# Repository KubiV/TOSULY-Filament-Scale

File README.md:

# TOSULY ALFA (V0.1)
## _DIY Filament scale integrated into filament holder_

Do It Yourself Filament Spool Scale which is integrated into the filament holder so you can easily monitor your remaining filament. By default it is not using batteries so you can hook it up straight to the printer/power suply. Optionaly you can add battery by soldering extension wires to prepared pads and than attach battery. 

## Features

- Open-source
- Custom PCB
- OLED 0.96 inch display
- Buttons (one under the display so it clicks when you push the display)
- By double-clicking button subtract spool dry mass
- Powered by Arduino Nano
- Compatible with stock Ender 3 spool holder, Prusa Original frame

## Needed

- 4x M3 screws (15mm for mounting PCBs)
- 2x M3 nuts (rectangle PCB mounting)
- 4x M4 screws (approx. 10 mm, and 2 with flat head)
- Custom PCB
- 7x1 horizontal pin header 2.54 mm pitch
- Arduino Nano
- USB cable (according on Arduino Nano variant)
- A DC-DC step-down converter and USB port for connecting the USB cable
- Load Cell 5 kg
- HX711 AD Module Weight Sensor
- 0.96 Inch OLED Module I2C
- 3x buttons 6 mm
- 3 resistor axial
- 3D printed parts (Upper, Body, Nut, Cover)

## Load cell

Compatible with both load cell designs - 12.7 x 12.7 x 75mm (type 1) or 12.7 x 12.7 x 80mm (type 2), holes for M4 bolts and two holes for M5 holes (type 2).

## 3D Printable parts

Mounting screw has 24 mm i diameter with according thread.

V02 design inspired by https://youtu.be/WO-hR7okl3k

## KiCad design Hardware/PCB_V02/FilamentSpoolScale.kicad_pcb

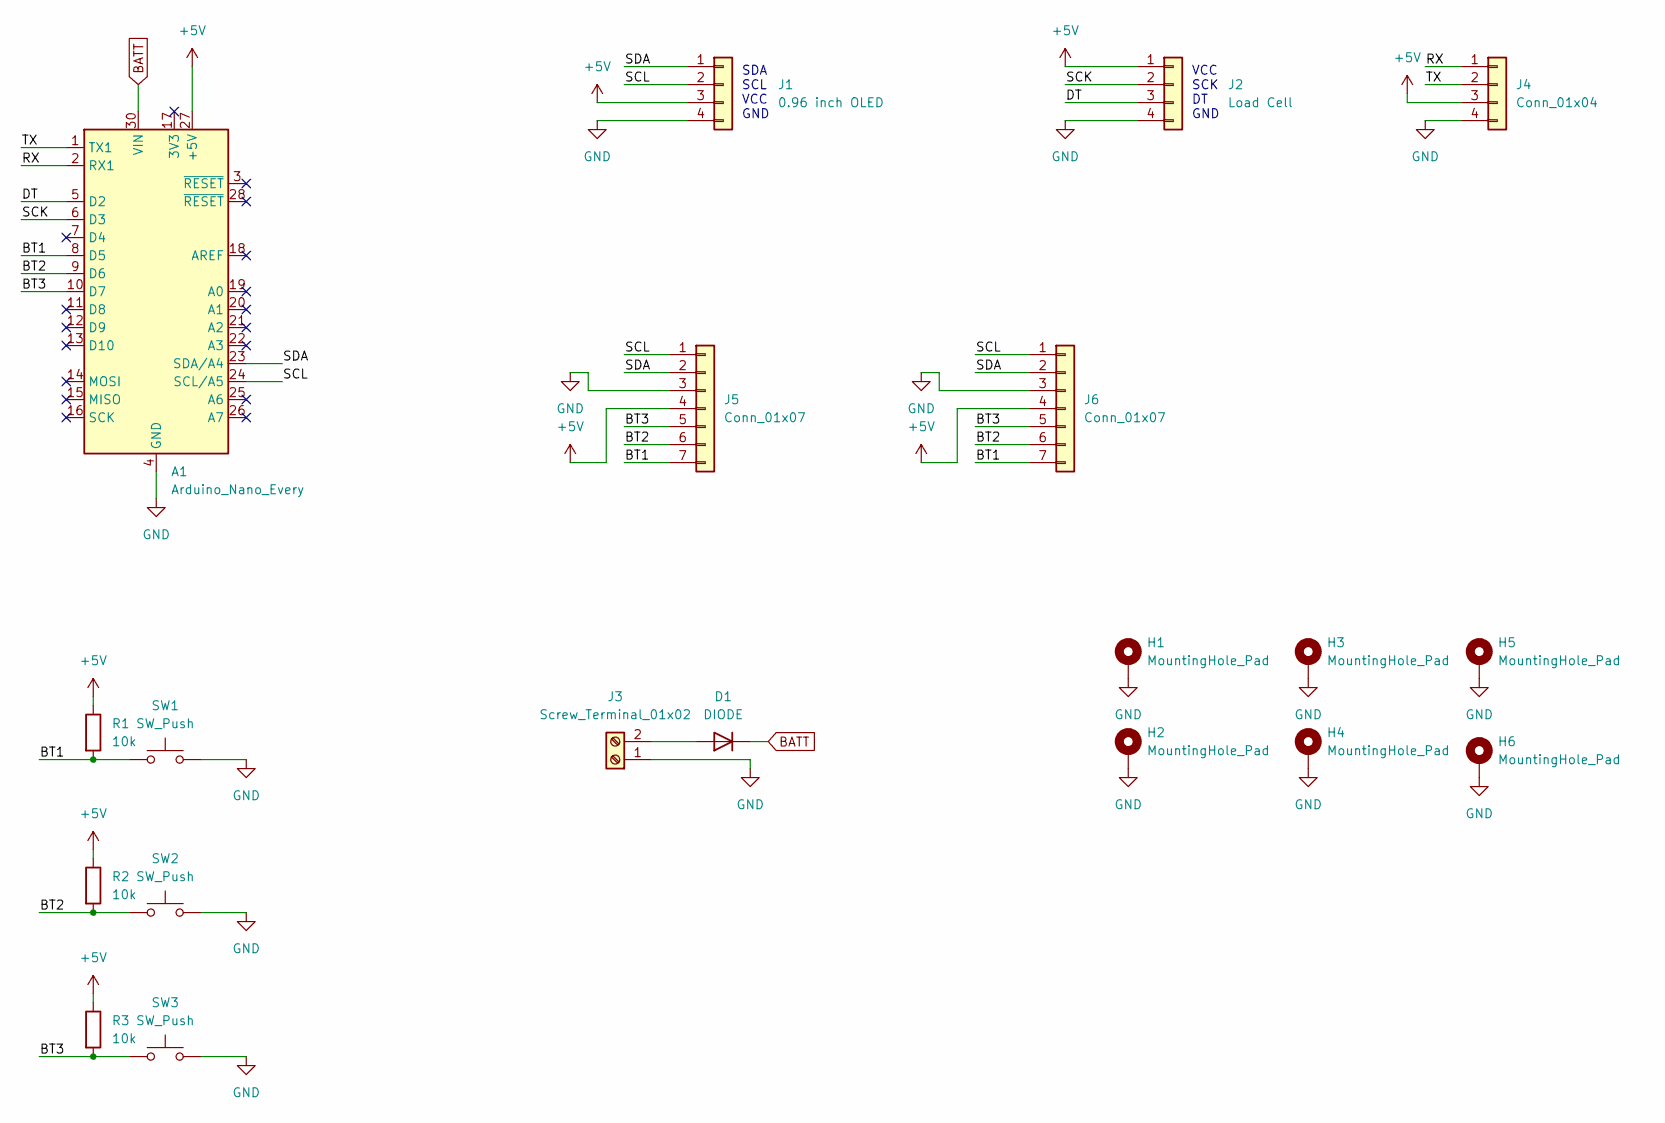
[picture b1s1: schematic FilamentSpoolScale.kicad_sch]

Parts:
A1: Arduino_Nano_Every; Arduino_Nano
D1: DIODE; D_DO-41_SOD81_P7.62mm_Horizontal
H1, H2, H3, H4, H5, H6: MountingHole_Pad; MountingHole_3.2mm_M3_DIN965_Pad_TopBottom
J1: 0.96 inch OLED; 0.96 inch OLED I2C
J2: Load Cell; LoadCellAmplifier
J3: Screw_Terminal_01x02; TerminalBlock_4Ucon_1x02_P3.50mm_Horizontal
J4: Conn_01x04; PinHeader_1x04_P2.54mm_Vertical
J5, J6: Conn_01x07; PinHeader_1x07_P2.54mm_Vertical
R1, R2, R3: 10k; R_Axial_DIN0207_L6.3mm_D2.5mm_P10.16mm_Horizontal
SW1, SW2, SW3: SW_Push; SW_PUSH_6mm_H4.3mm

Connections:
+5V: A1.27 (+5V), J1.3, J2.1, J4.3, J5.4, J6.4, R1.1, R2.1, R3.1
/BT1: A1.8 (D5), J5.7, J6.7, R1.2, SW1.1
/BT2: A1.9 (D6), J5.6, J6.6, R2.2, SW2.1
/BT3: A1.10 (D7), J5.5, J6.5, R3.2, SW3.1
/DT: A1.5 (D2), J2.3
/RX: A1.2 (RX1), J4.1
/SCK: A1.6 (D3), J2.2
/SCL: A1.24 (SCL/A5), J1.2, J5.1, J6.1
/SDA: A1.23 (SDA/A4), J1.1, J5.2, J6.2
/TX: A1.1 (TX1), J4.2
BATT: A1.30 (VIN), D1.2 (K)
GND: A1.4 (GND), A1.29 (GND), H1.1, H2.1, H3.1, H4.1, H5.1, H6.1, J1.4, J2.4, J3.1, J4.4, J5.3, J6.3, SW1.2, SW2.2, SW3.2
unnamed: D1.1 (A), J3.2

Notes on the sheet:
SDA SCL VCC GND
VCC SCK DT GND

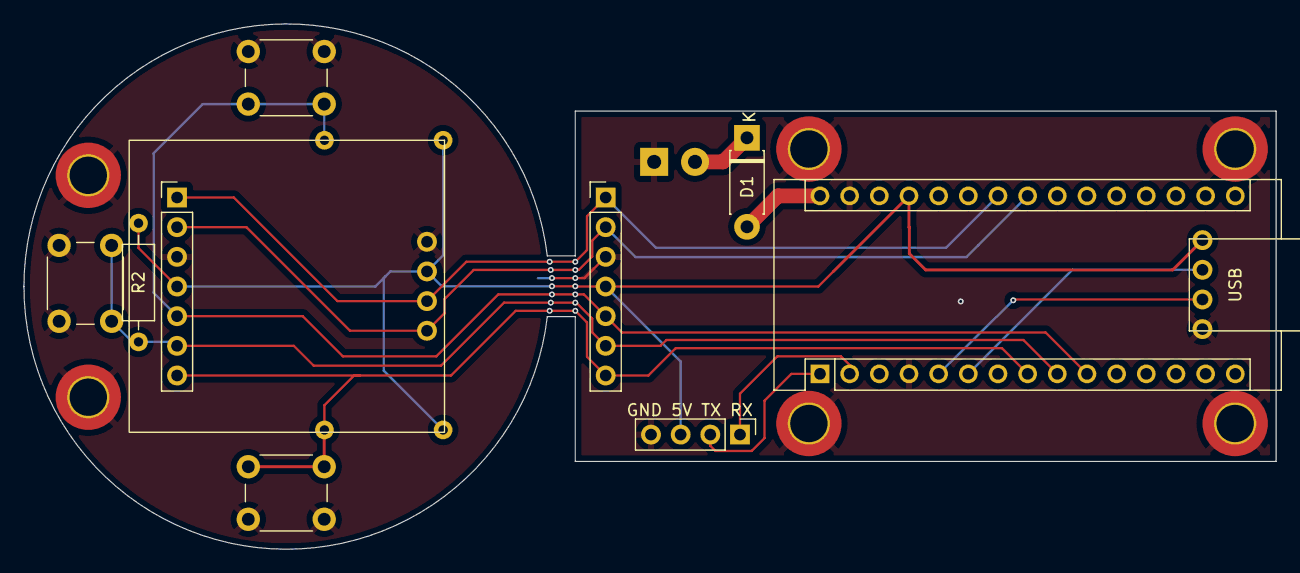
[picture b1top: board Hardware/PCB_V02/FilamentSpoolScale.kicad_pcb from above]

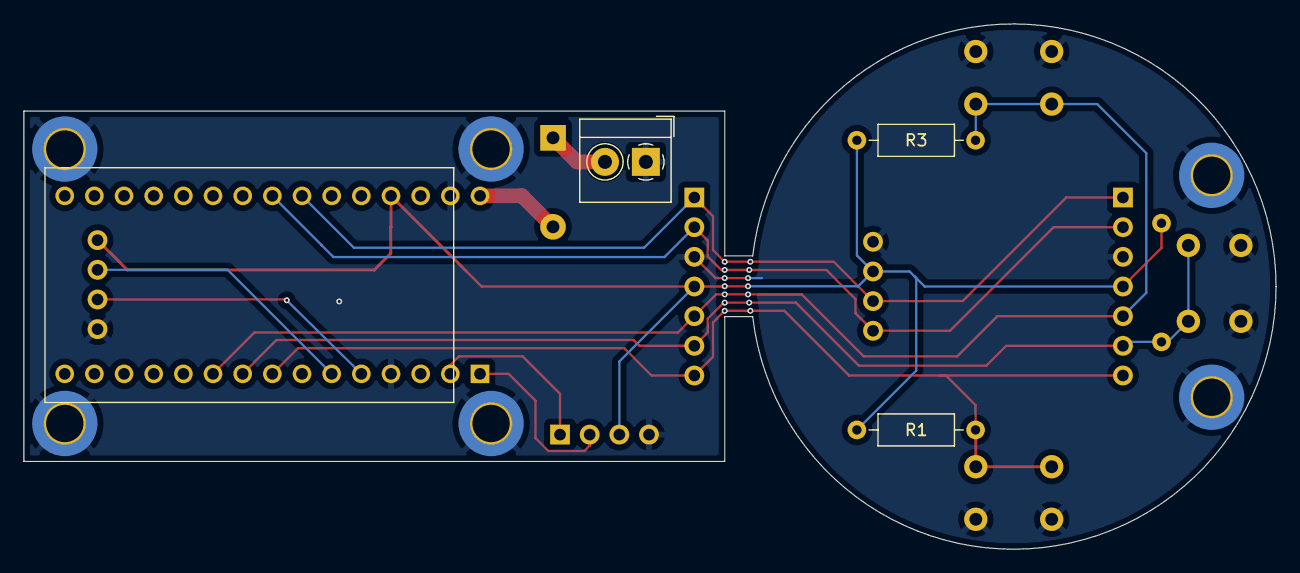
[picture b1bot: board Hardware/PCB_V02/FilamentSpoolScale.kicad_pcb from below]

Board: 2 copper layers, 107.2 x 45.0 mm, 20 parts (4 on the bottom side), 13 nets.

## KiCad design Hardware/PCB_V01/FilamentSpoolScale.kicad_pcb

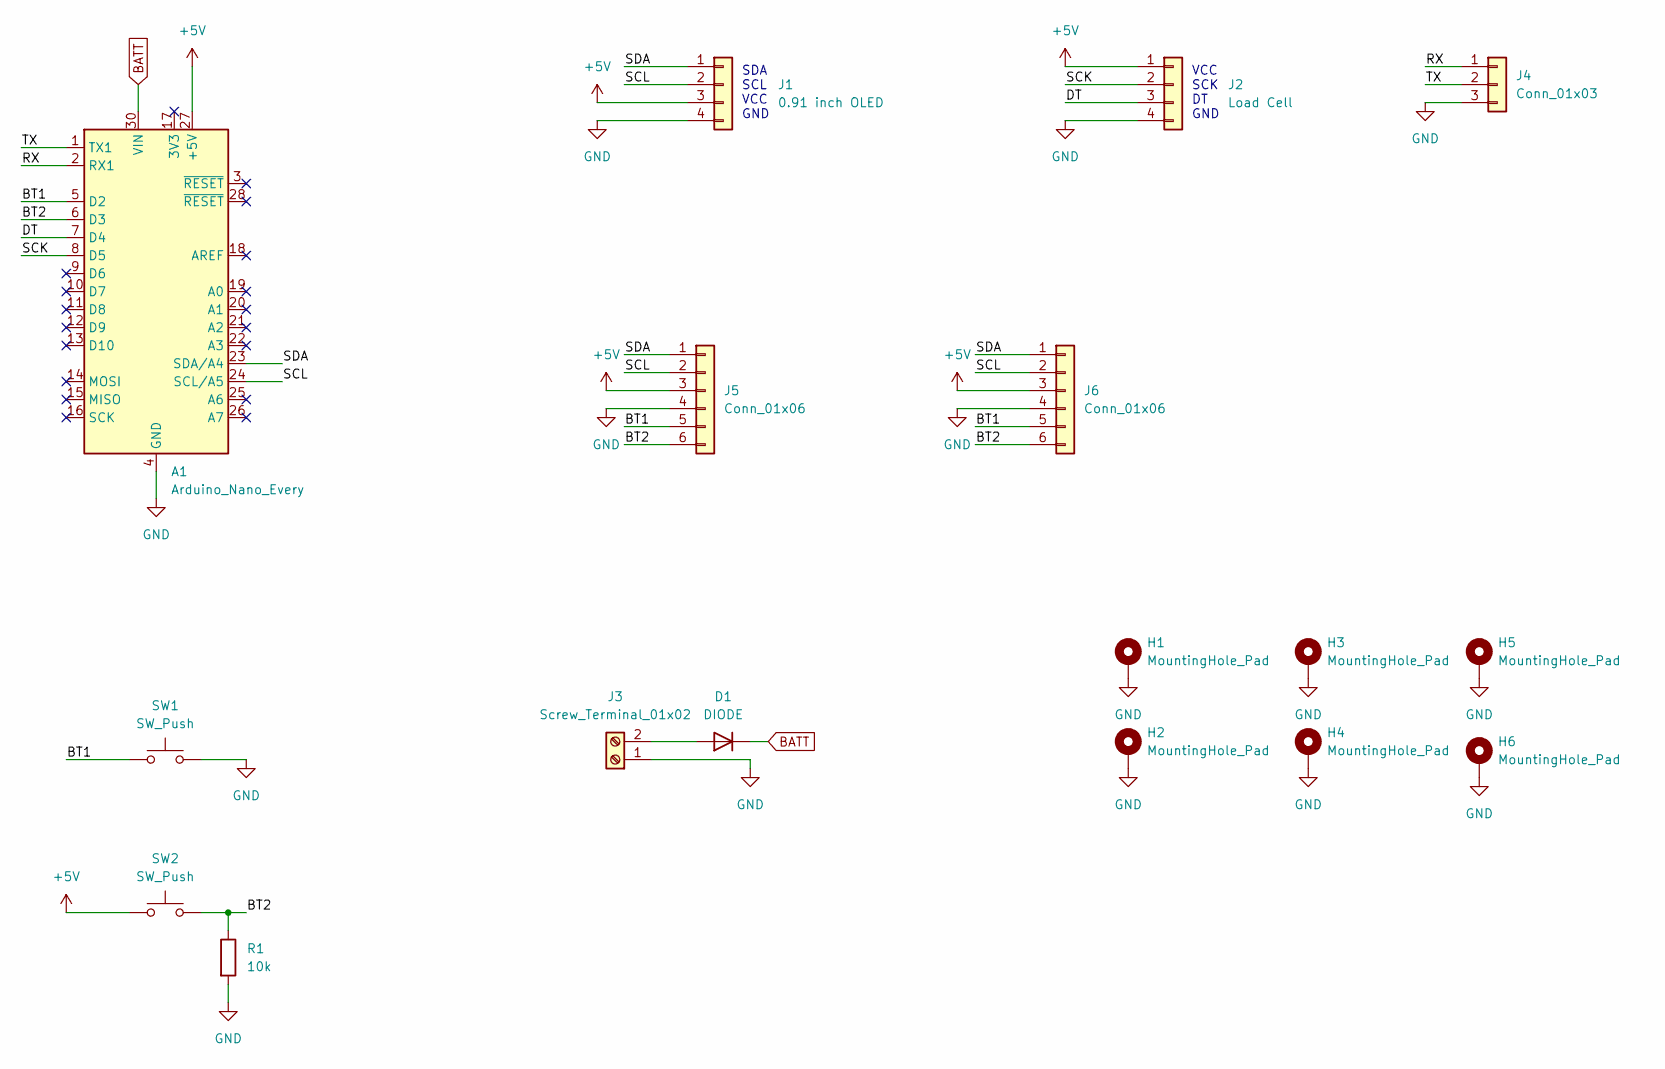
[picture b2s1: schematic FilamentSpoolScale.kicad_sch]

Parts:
A1: Arduino_Nano_Every; Arduino_Nano
D1: DIODE; D_DO-41_SOD81_P7.62mm_Horizontal
H1, H2, H3, H4, H5, H6: MountingHole_Pad; MountingHole_3.2mm_M3_DIN965_Pad_TopBottom
J1: 0.91 inch OLED; 0.91inch OLED
J2: Load Cell; LoadCellAmplifier
J3: Screw_Terminal_01x02; TerminalBlock_4Ucon_1x02_P3.50mm_Horizontal
J4: Conn_01x03; PinHeader_1x03_P2.54mm_Vertical
J5: Conn_01x06; PinHeader_1x06_P2.54mm_Vertical
J6: Conn_01x06; PinHeader_1x06_P2.54mm_Horizontal
R1: 10k; R_Axial_DIN0207_L6.3mm_D2.5mm_P10.16mm_Horizontal
SW1, SW2: SW_Push; SW_PUSH_6mm_H4.3mm

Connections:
+5V: A1.27 (+5V), J1.3, J2.1, J5.3, J6.3, SW2.1
/BT1: A1.5 (D2), J5.5, J6.5, SW1.1
/BT2: A1.6 (D3), J5.6, J6.6, R1.1, SW2.2
/DT: A1.7 (D4), J2.3
/RX: A1.2 (RX1), J4.1
/SCK: A1.8 (D5), J2.2
/SCL: A1.24 (SCL/A5), J1.2, J5.2, J6.2
/SDA: A1.23 (SDA/A4), J1.1, J5.1, J6.1
/TX: A1.1 (TX1), J4.2
BATT: A1.30 (VIN), D1.2 (K)
GND: A1.4 (GND), A1.29 (GND), H1.1, H2.1, H3.1, H4.1, H5.1, H6.1, J1.4, J2.4, J3.1, J4.3, J5.4, J6.4, R1.2, SW1.2
unnamed: D1.1 (A), J3.2

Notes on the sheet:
SDA SCL VCC GND
VCC SCK DT GND

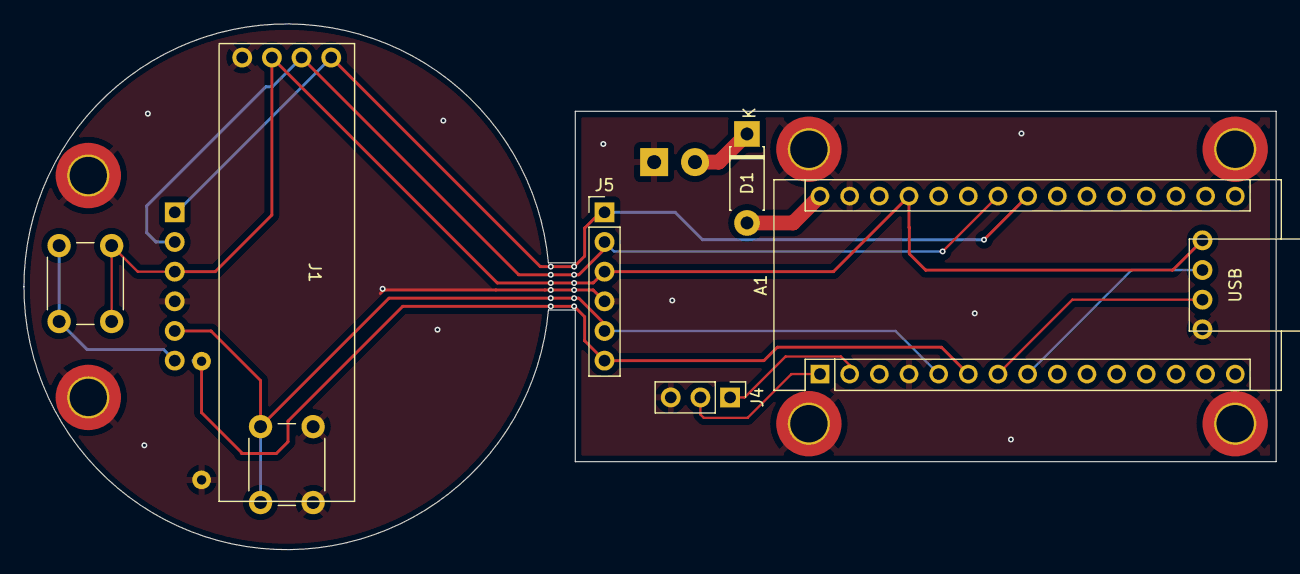
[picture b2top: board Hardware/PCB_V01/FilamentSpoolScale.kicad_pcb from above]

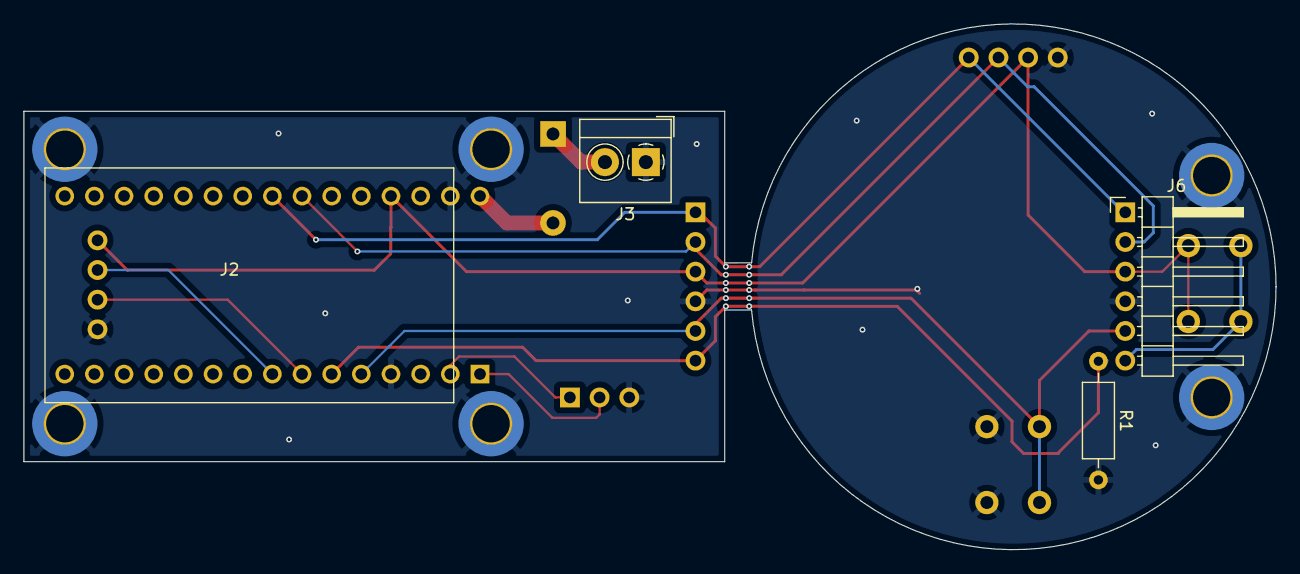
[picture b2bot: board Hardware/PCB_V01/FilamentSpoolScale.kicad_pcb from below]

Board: 2 copper layers, 107.2 x 45.0 mm, 17 parts (4 on the bottom side), 12 nets.

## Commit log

2023-02-23 Reorganisation
2023-02-23 Addition of 2nd button (backup button)
2023-02-24 Board design
2023-02-26 Testing Software and hw changes
2023-02-26 Firmware 0.1
2023-02-26 Preparing for public alfa release (V0.1)
2023-02-26 readme update
2023-02-26 readme changes
2023-02-26 PCB schematic rearangement
2023-02-27 HW V0.2 and Adaptor for Prusa Original 3D printer
2023-02-27 readme
2023-02-27 individual 3D printed parts
2023-03-05 V02 Hardware and reorganisation
2023-03-05 PCB PDF edit
2023-03-05 Printable files
2023-03-25 PCB correction
2023-03-26 V02 hw
2023-03-27 Code from InterlinkKnight
    source: https://www.instructables.com/Digital-Spool-Holder-with-Scale/
2023-03-27 Code changes
